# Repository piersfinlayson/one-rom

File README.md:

# One ROM

**[One ROM](https://onerom.org) - One ROM To Rule Them All**

The most flexible and powerful ROM replacement for your retro computer.  A single Raspberry Pi
RP2350-base board in the footprint of the original chip emulates 24, 28, 32 and
40 pin mask ROMs, EPROMs, EEPROMs, bipolar PROMs and some SRAM — and then does
things the original never could.  It serves several ROM sockets at once, switches
images at runtime, reprograms over USB without leaving the socket, talks back to
the machine it is installed in, and runs your own code as plugins.

Thousands of One ROMs are installed in Commodore 64s, VIC-20s, PETs, Amigas, BBCs, Ataris, TIs, Apple IIs,
disk drives, IBM PCs, pinball machines, drum machines, synthesizers and more.  It is
open source hardware and software, it is cheap to make, and it is actively
maintained and developed.

## New to One ROM?

**Start at [onerom.org](https://onerom.org).**  That is where the project is
explained and supported:

- [What One ROM is and why](https://onerom.org) — the overview, with pictures
- [Getting started](https://onerom.org/start/) — install it, program it, use it
- [Buy one](https://onerom.org/buy) — known vendors, if you'd rather not fab
  your own
- [Program from your browser](https://onerom.org/web) — no software to install

**The rest of this README is for people who want to build One ROM, hack on it,
or build things on top of it.**  If you just want a working ROM replacement, [onerom.org](https://onerom.org) will get you there faster.

## Ways in

One ROM is designed to be extended in many different ways.

| I want to… | Start here | Steps |
|------------|------------|------------|
| Drive a device from scripts or my own tooling | [Programming a One ROM](#programming-a-one-rom), [CLI manual](docs/CLI-MANUAL.md) | Install and run the CLI |
| Fab and assemble existing boards | [hardware/pcb](hardware/pcb/README.md) | Upload gerbers and BOM/POS files to a fab |
| Commission boards I've made | [Commissioning](docs/COMMISSIONING.md) | Request an authorised signing key or submit a signing request for a board |
| Build the firmware myself | [Building from source](#building-from-source) | Use `make` or the build container |
| Use the header pins as GPIOs — reset the host, drive a line | [Driving the host](#driving-the-host--gpio-and-reset) | One command, plus a wire for host reset |
| Add support for a chip type One ROM doesn't know | [Adding a chip type](docs/ADDING-CHIP-TYPES.md) | A JSON entry plus one line of Rust or a firmware and tooling update if no existing serving algorithm fits |
| Add support for a new board revision | [rust/config/json](rust/config/json/README.md) | A new JSON file once the board is designed |
| Write a plugin — from scratch, or from a working one | [Plugins](#plugins), [firmware/ora/examples](firmware/ora/examples) | C, against a stable API |
| Talk to the retro machine from the ROM socket | [RBCP](#rbcp--talking-to-the-host-system) | 6502 and 68000 host code provided |
| Build host-side tools of my own | [Rust crates](#rust-crates) | Rust, on published crates |
| Read and test real ROM chips | [One ROM Lab](#one-rom-lab) | Flash Lab to a spare Fire board |
| Add a serving algorithm, or change how serving works | [How the firmware works](#how-the-firmware-works) | Bare metal C, PIO and DMA, plus Rust tooling |
| Design a new board | [hardware/pcb](hardware/pcb/README.md) | KiCad |

## Hardware

One ROM comes in two families:

- **Fire** — RP2350, in 24, 28, 32 and 40 pin variants, latest boards include an
  RGB NeoPixel.  All development happens for these boards.
- **Ice** — STM32F4, 24 pin only.  Legacy: still supported with 0.6.x firmware,
  but it is not being enhanced.  The 0.7.x firmware and the CLI do not
  support it.

<div align="center">
    
</div>

<div align="center">
    
</div>

All the design files needed to manufacture your own are in
[hardware/pcb](hardware/pcb).  Start with the
[recommended revisions](hardware/pcb/README.md#recommended-revisions) and
read the fabrication notes in the same file before you order.  Boards can be
fabbed and assembled at JLCPCB and other manufacturers cheaply.

<div align="center">
    
</div>

<p align="center"><em>Three One ROM Fire 24s in a Commodore 64, serving BASIC,
KERNAL and the character ROM.</em></p>

## Programming a One ROM

There are three tools, all doing the same job over USB:

- **[One ROM Web](https://onerom.org/web)** — browser based, nothing to install,
  the best choice for most people.
- **[One ROM CLI](https://onerom.org/cli)** — the full device tool, and what the
  examples below use ([rust/cli](rust/cli)).
- **[One ROM Studio](https://onerom.org/studio)** — native desktop GUI for
  Windows, macOS and Linux ([rust/studio](rust/studio)).

The CLI is the complete interface: everything the device can do is reachable from
it.  Full reference in the [CLI manual](docs/CLI-MANUAL.md).

Find what is connected:

```bash
onerom scan
```

Build an image from a config file and flash it:

```bash
onerom program --config onerom-config/vic20-pal.json
```

Program chips straight from the command line, without a config file, adding the
USB plugin so the device stays on the bus while it serves:

```bash
onerom program --slot file=kernal.901227-03.bin,type=2364,cs1=active-low --plugin usb
```

Build a firmware binary without touching a device, and look inside one:

```bash
onerom firmware build --config onerom-config/vic20-pal.json --board fire-24-e --output /tmp/onerom.bin
onerom firmware inspect --firmware /tmp/onerom.bin
```

Read and write the ROM image live, while the host is running from it:

```bash
onerom peek live --address 0x100 --length 64
onerom poke live --address 0x100 --byte 0xEA
```

## Driving the host — GPIO and reset

The image select and X pins are not just jumpers.  They are GPIOs, and
One ROM will drive them for you — which means the ROM socket becomes a way to
manipulate the machine it is plugged into.

Run a wire from a pin to the host's reset line and you can reset the machine
after flashing a new image:

```bash
onerom control reset --pin sel_c
```

`sel_c` is a common choice — more boards have it than have X pins, and it is 5V
tolerant where it exists.  Any pin works with `--pin`.

<div align="center">
    
</div>

<p align="center"><em>A One ROM Fire 40 in an Amiga A500, with <code>Sel_C</code>
wired to the 68000's reset line.</em></p>

You can see what every pin is and what it is currently doing:

```bash
onerom inspect gpio --all
onerom inspect socket --chip-type 2364 --gpio
```

The same GPIOs are available to plugins, so a plugin can drive them
autonomously — hold the host in reset until something is ready, blink an
external LED on ROM activity, or drive whatever you have wired up.

## Plugins

Serving runs entirely on PIO and DMA, so both CPU cores are free.  Plugins are
separate binaries, written in C against a stable API in
[firmware/ora](firmware/ora), that run on those cores *while serving continues*.
Two run at once.  This is how One ROM gains functionality without needing to
fork the core firmware.

There are two types, **system** and **user**.  The difference is resources, not
authorship — each is built for a different flash slot with a different RAM and
stack allocation, and you can write either.  System is intended for official One
ROM plugins such as the USB stack, but nothing stops you replacing it with your
own.

| Plugin | Type | What it does |
|--------|------|--------------|
| [usb](plugins/system/usb) | system | The device's own USB stack, so a running One ROM stays on the bus.  Exposes the ROM being served for live read and write, and the `picobootx` extended PICOBOOT interface. |
| [host-control](plugins/user/host-control) | user | A full [RBCP](#rbcp--talking-to-the-host-system) implementation. |
| [rgb](plugins/user/rgb) | user | Cycles the NeoPixel on RGB boards.  Superseded by the USB plugin's RGB support, reached with `onerom control rgb`. |
| [activity](plugins/user/activity) | user | Blinks the status LED when the host is reading the ROM. |
| [blink](plugins/user/blink) | user | Minimal example. |

The firmware passes each plugin a lookup function at startup.  The plugin calls
it with the ID of the facility it wants, and gets back a function pointer.
Available that way: status LED and GPIO control, device and firmware metadata,
logging, memory allocation, the ROM and RAM slots being served, and the address
monitor that reports what the host is reading — which is what RBCP is built on.
New IDs are only ever added, never changed, and each plugin declares the minimum
firmware version it needs, which the firmware enforces before launching it.

Start with [plugins/README.md](plugins/README.md) for how plugins are built and
configured, [firmware/ora/api.h](firmware/ora/api.h) for the API, and
[firmware/ora/examples](firmware/ora/examples) for worked examples — including
one that patches the C64 kernal live and one that drives an LED from character
ROM accesses.

## RBCP — talking to the host system

The [ROM Bus Control Protocol](https://github.com/piersfinlayson/rom-bus-control-protocol)
is bidirectional communication between a retro machine and the ROM emulator
installed in it, carried over nothing but the ROM's own address and data buses.
No extra wiring.  The machine reads and writes ROM addresses, and One ROM
interprets them.

That opens up things a ROM socket has no business being able to do:

- remote debugging of code running on real hardware
- ROM-based bootloaders — `grub` for the C64
- dynamic patching of games and demos as they run

The device side is the [host-control](plugins/user/host-control) plugin.  The
specification lives in the RBCP repository, along with reference host
implementations for 6502 and 68000 — generic routines plus sample C64 kernal and
Amiga Kickstart bootloaders.

## One ROM Lab

[One ROM Lab](rust/lab/README.md) is alternate firmware for a spare Fire board that turns
its ROM socket into a bus reader and tester.  Flash it, connect over USB, and you
get an interactive shell.

Read a real chip in the socket, as a checksum, a hexdump or Intel HEX.  Verify
that a One ROM under test serves the right bytes and tristates its data lines
when deselected.  Auto-detect chip select polarity on an unmarked mask ROM by
brute-forcing the combinations.  Dump the board's pin map, socket pin to signal
to GPIO.  It is what Fire 40 boards are tested with before they ship.

```bash
cd rust/lab && scripts/flash.sh
```
## Building from source

Dependencies are listed in [INSTALL.md](INSTALL.md), or use the
[build container](ci/docker/README.md).  The ARM and
Emscripten toolchain versions are pinned (`ci/arm-toolchain-version`,
`ci/emscripten-version`), as are the documentation tools that render the PDF
editions (`ci/pandoc-version`, `ci/weasyprint-version`), so a firmware binary is byte-identical wherever it is
built.

Build the base firmware:

```bash
make
```

That produces `firmware/build/onerom-rp235x.bin` — one binary, for every Fire
board.  The ROM images, chip configuration and plugins are composed onto it by
the host-side tools.  To flash *your* build rather than a downloaded release,
pass it explicitly:

```bash
onerom program --config onerom-config/vic20-pal.json --base-firmware firmware/build/onerom-rp235x.bin
```

## How the firmware works

Worth knowing before you go digging in [firmware/](firmware):

**It is fully bare metal.**  No SDK, no HAL — not pico-sdk, not a vendor library.
C with its own startup code and its own linker scripts to keep it lean.

**Serving runs on PIO and DMA.**  The RP2350's PIO state machines watch the
address and chip select lines and DMA the right byte onto the data pins.  The CPU
is not in the critical path, which is what leaves both cores free for plugins.

**The chip type is not compiled in.**  The firmware knows nothing about a 2364 or
a 27C400.  It has a small set of parameterised serving algorithms, and the
host-side generator works out which algorithm and what arguments a given chip on
a given board needs, then writes that into the firmware metadata.

**It is one binary for all boards.**  Board differences are metadata too.

**Bad configuration is visible, not silent.**  An image the firmware cannot make
sense of drops it into limp mode, with an special LED blink pattern.

**The PIO programs are assembled on the device, at boot.**  Which program is
needed depends on the chip, the board's pin mapping and the configuration in
flash, none of which are known at build time.
[apio](https://github.com/piersfinlayson/apio) assembles them in C at runtime,
and disassembles them so a generated program can be read back and checked.

## Regression tested off-hardware

Every push runs the **real firmware C** — the source that ships on devices, not a
model of it — compiled for the host and linked against
[epio](https://github.com/piersfinlayson/epio), a cycle-exact RP2350 PIO
emulator, then driven over emulated bus cycles.

The sweep is hundreds of test runs covering all Fire board revisions, all supported
chip types, every configuration shape the firmware offers — single, banked,
multi-chip, 16-bit — and every chip select polarity combination.  Every address
of every image is compared against an independent copy, which is 10s of
millions of byte-level comparisons, plus checks that the data bus tristates for every
non-selected control line combination.

The plugin API is covered down to all API IDs, and the host-control plugin's own C source is run against a full suite of
conformance tests whose basis is the protocol specification rather than the
implementation.

CS-to-data latency is asserted to the exact cycle in **both**
directions, so serving getting a cycle slower — or a cycle faster, which would
mean the check had stopped discriminating — fails the build.

What it does not do today is anything analogue — voltage levels, bus loading,
propagation delay at a real pin — or USB.  Those need a board, which is what
[One ROM Lab](#one-rom-lab) is for.

## Rust crates

The host-side tooling is a Cargo workspace in [rust/](rust).  The crates marked
published are on crates.io, for host-side Rust development.

| Crate | Published | What it is for |
|-------|:---------:|----------------|
| [`onerom-gen`](rust/gen) | ✓ | Generates ROM images and firmware metadata.  The heart of the toolchain — turns a config plus some ROM files into something flashable. |
| [`onerom-config`](rust/config) | ✓ | The config model: chip types, board definitions, pin maps, JSON schema. |
| [`onerom-fw`](rust/fw) | ✓ | Fetches One ROM base firmware and ROM images. |
| [`onerom-fw-parser`](rust/fw-parser) | ✓ | Reads metadata back out of a firmware binary — what chips, what board, what version. |
| [`onerom-metadata`](rust/metadata) | ✓ | The embedded metadata schema itself. |
| [`onerom-lab-metadata`](rust/lab-metadata) | ✓ | One ROM Lab's metadata structures. |
| [`onerom-lab-parser`](rust/lab-parser) | ✓ | Reads One ROM Lab's metadata structures from a device or an image. |
| [`onerom-metadata-gen`](rust/metadata-gen) | ✓ | Turns a metadata schema into C headers and Rust source. |
| [`onerom-cli`](rust/cli) | ✓ | Everything the CLI does, minus the command line parsing.  Build on it rather than reimplementing USB device logic. The CLI binary is released at [onerom.org/cli](https://onerom.org/cli). |
| [`onerom-app`](rust/app) | ✓ | Transport-free logic shared by the CLI, Studio and the web tools. |
| [`onerom-studio`](rust/studio) | | The desktop GUI, released at [onerom.org/studio](https://onerom.org/studio). |
| [`onerom-lab`](rust/lab) | | One ROM Lab, above. |
| [`onerom-lab-bus`](rust/lab-bus) | | One ROM Lab's host bus timing. |
| [`onerom-signing-server`](rust/signing-server) | | Signs commissioning instances. |
| [`onerom-lens`](rust/lens) | | One ROM Lens — compiles the firmware emulator to WebAssembly and draws PIO and DMA activity as waveforms in a browser, cycle by cycle. |
| [`onerom-fw-emulator`](rust/fw-emulator) | | Compiles and runs the real firmware C on a host, PIOs and all. |
| [`onerom-fw-tester`](rust/fw-tester) | | Drives the emulator with generated configurations and checks the results. |
| [`onerom-plugin-tester`](rust/plugin-tester) | | The harness a plugin tester is built from — runs a plugin's own C against the emulated firmware. |
| [`onerom-rbcp-host`](rust/rbcp-host) | | An RBCP host. One ROM Lab uses it to query a One ROM over the ROM bus. |
| [`onerom-rbcp-tester`](rust/rbcp-tester) | | Drives the host-control plugin over emulated ROM bus cycles, as an RBCP host would. |
| [`onerom-usb-tester`](rust/usb-tester) | | Drives the USB system plugin's commands, log forwarding and GPIO control. |
| [`onerom-fw-driver`](rust/fw-driver), [`onerom-fw-geometry`](rust/fw-geometry) | | Pin geometry and GPIO bitmask helpers, shared and dependency-free by design. |
| [`fw-config-gen`](rust/fw-config-gen), [`schema-gen`](rust/schema-gen) | | Code and schema generators. |
| [`doc-gen`](rust/doc-gen) | | Checks the values in `docs/` and `onerom-config/README.md`. |

For in-browser use, [one-rom-wasm](https://github.com/piersfinlayson/one-rom-wasm)
wraps `onerom-gen` as WASM, and is what the
[browser programmer](https://onerom.org/web) in
[one-rom-site](https://github.com/piersfinlayson/one-rom-site) is built on.

## What is in this repository

| Directory | Contents |
|-----------|----------|
| [`firmware/`](firmware) | The core firmware: C and Thumb assembly, bare metal.  `ora/` is the plugin API. |
| [`plugins/`](plugins) | System and user plugins. |
| [`rust/`](rust) | The Cargo workspace — CLI, Studio, generators, emulator, Lab, Lens. |
| [`hardware/pcb/`](hardware/pcb) | KiCad designs, per board revision, verified and unverified. |
| [`onerom-config/`](onerom-config) | Ready-made JSON configs for some common systems, and the config schema. |
| [`docs/`](docs) | Documentation, including the generated chip and compatibility references. |
| [`ci/`](ci) | Build, test and lint scripts, and the reproducible build container. |
| [`images/`](images) | Test ROM images. |
| [`demo/`](demo) | Demonstration programs for the retro side. |

## Documentation

| Topic | Description |
|-------|-------------|
| [CLI Manual](docs/CLI-MANUAL.md) | Complete reference for the `onerom` command line tool. |
| [Chip Types](docs/CHIP-TYPES.md) | Every chip type One ROM knows about, with pinouts and control lines. |
| [Compatibility](docs/COMPATIBILITY.md) | Which chips each hardware variant can emulate, and at what flash cost. |
| [Adding a Chip Type](docs/ADDING-CHIP-TYPES.md) | Teaching One ROM to emulate a chip it does not yet know. |
| [Commissioning](docs/COMMISSIONING.md) | Setting a One ROM's hardware settings. |
| [Image Selection](docs/IMAGE-SELECTION.md) | Telling One ROM which installed image to serve. |
| [Logging](docs/LOGGING.md) | Reading One ROM's log, over USB or with a debug probe. |
| [Image Sets](docs/MULTI-ROM-SETS.md) | Serving several ROMs at once, and dynamic bank switching. |
| [Plugins](plugins/README.md) | Building, configuring and writing plugins. |
| [Build Container](ci/docker/README.md) | Building the firmware reproducibly in Docker. |
| [ROMs Glorious ROMs](docs/ROMS-GLORIOUS-ROMS.md) | Everything you wanted to know about 23/27 series ROMs but were afraid to ask. |
| [Second Flash](docs/SECOND-FLASH.md) | How One ROM handles a second flash chip connected to the RP2350 |
| [Changelog](CHANGELOG.md) | What changed, and when. |

The CLI manual, chip type and compatibility references are also published as
PDFs, in A4 and US Letter, at [onerom.org/docs](https://onerom.org/docs/).

More in [docs/](docs) — flash layout, voltage levels, using a Pi Pico as
an SWD programmer — plus [INSTALL.md](INSTALL.md) for build dependencies and
[LICENSE.md](LICENSE.md).

## Videos

Why use One ROM:

The hardware family:

## Related repositories

| Repository | What it is |
|------------|------------|
| [rom-bus-control-protocol](https://github.com/piersfinlayson/rom-bus-control-protocol) | The RBCP specification, and 6502/68000 reference host implementations. |
| [one-rom-site](https://github.com/piersfinlayson/one-rom-site) | onerom.org, including the browser programmer. |
| [one-rom-images](https://github.com/piersfinlayson/one-rom-images) | images.onerom.org — firmware images, configs, plugin manifests. |
| [one-rom-wasm](https://github.com/piersfinlayson/one-rom-wasm) | WASM build of `onerom-gen`, for in-browser firmware generation. |
| [picoboot](https://github.com/piersfinlayson/picoboot) | Host-side Rust crate for the RP2350 PICOBOOT USB interface. |
| [picobootx](https://github.com/piersfinlayson/picobootx) | Device-side PICOBOOT extension, exposed by the USB plugin. |
| [apio](https://github.com/piersfinlayson/apio) | Runtime RP2350 PIO assembler and disassembler. |
| [epio](https://github.com/piersfinlayson/epio) | Cycle-exact RP2350 PIO emulator. |

## Problems

Raise an issue at the [project issues page](https://github.com/piersfinlayson/one-rom/issues)
or start a thread at [GitHub Discussions](https://github.com/piersfinlayson/one-rom/discussions).
Please include:

- your One ROM PCB type and revision (or a photo if you're unsure)
- the retro system you are using it with
- details of the problem.

## Contributing

Pull requests are welcome — firmware, tools, hardware and documentation.  If you
write a plugin you think others would want to use, consider contributing it
so it can be published.  The plugins publishing process is documented in
[plugins/CONTRIBUTIONS](plugins/CONTRIBUTIONS.md)

## License

See [LICENSE](LICENSE.md) for software and hardware licensing information, and
[ACKNOWLEDGEMENTS](ACKNOWLEDGEMENTS.md) for third party work One ROM builds on
or is compatible with.

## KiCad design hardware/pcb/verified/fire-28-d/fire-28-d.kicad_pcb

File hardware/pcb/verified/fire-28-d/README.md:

# Fire 28 Rev D

An upright USB-C variant of fire-28-c - the connector sticks up out of the board rather than lying flat, which helps where there is too little room at the edge of One ROM to plug in a cable.  It is not preferred over fire-28-c - the two connector orientations are complementary.

**Has components on both sides of the board.**

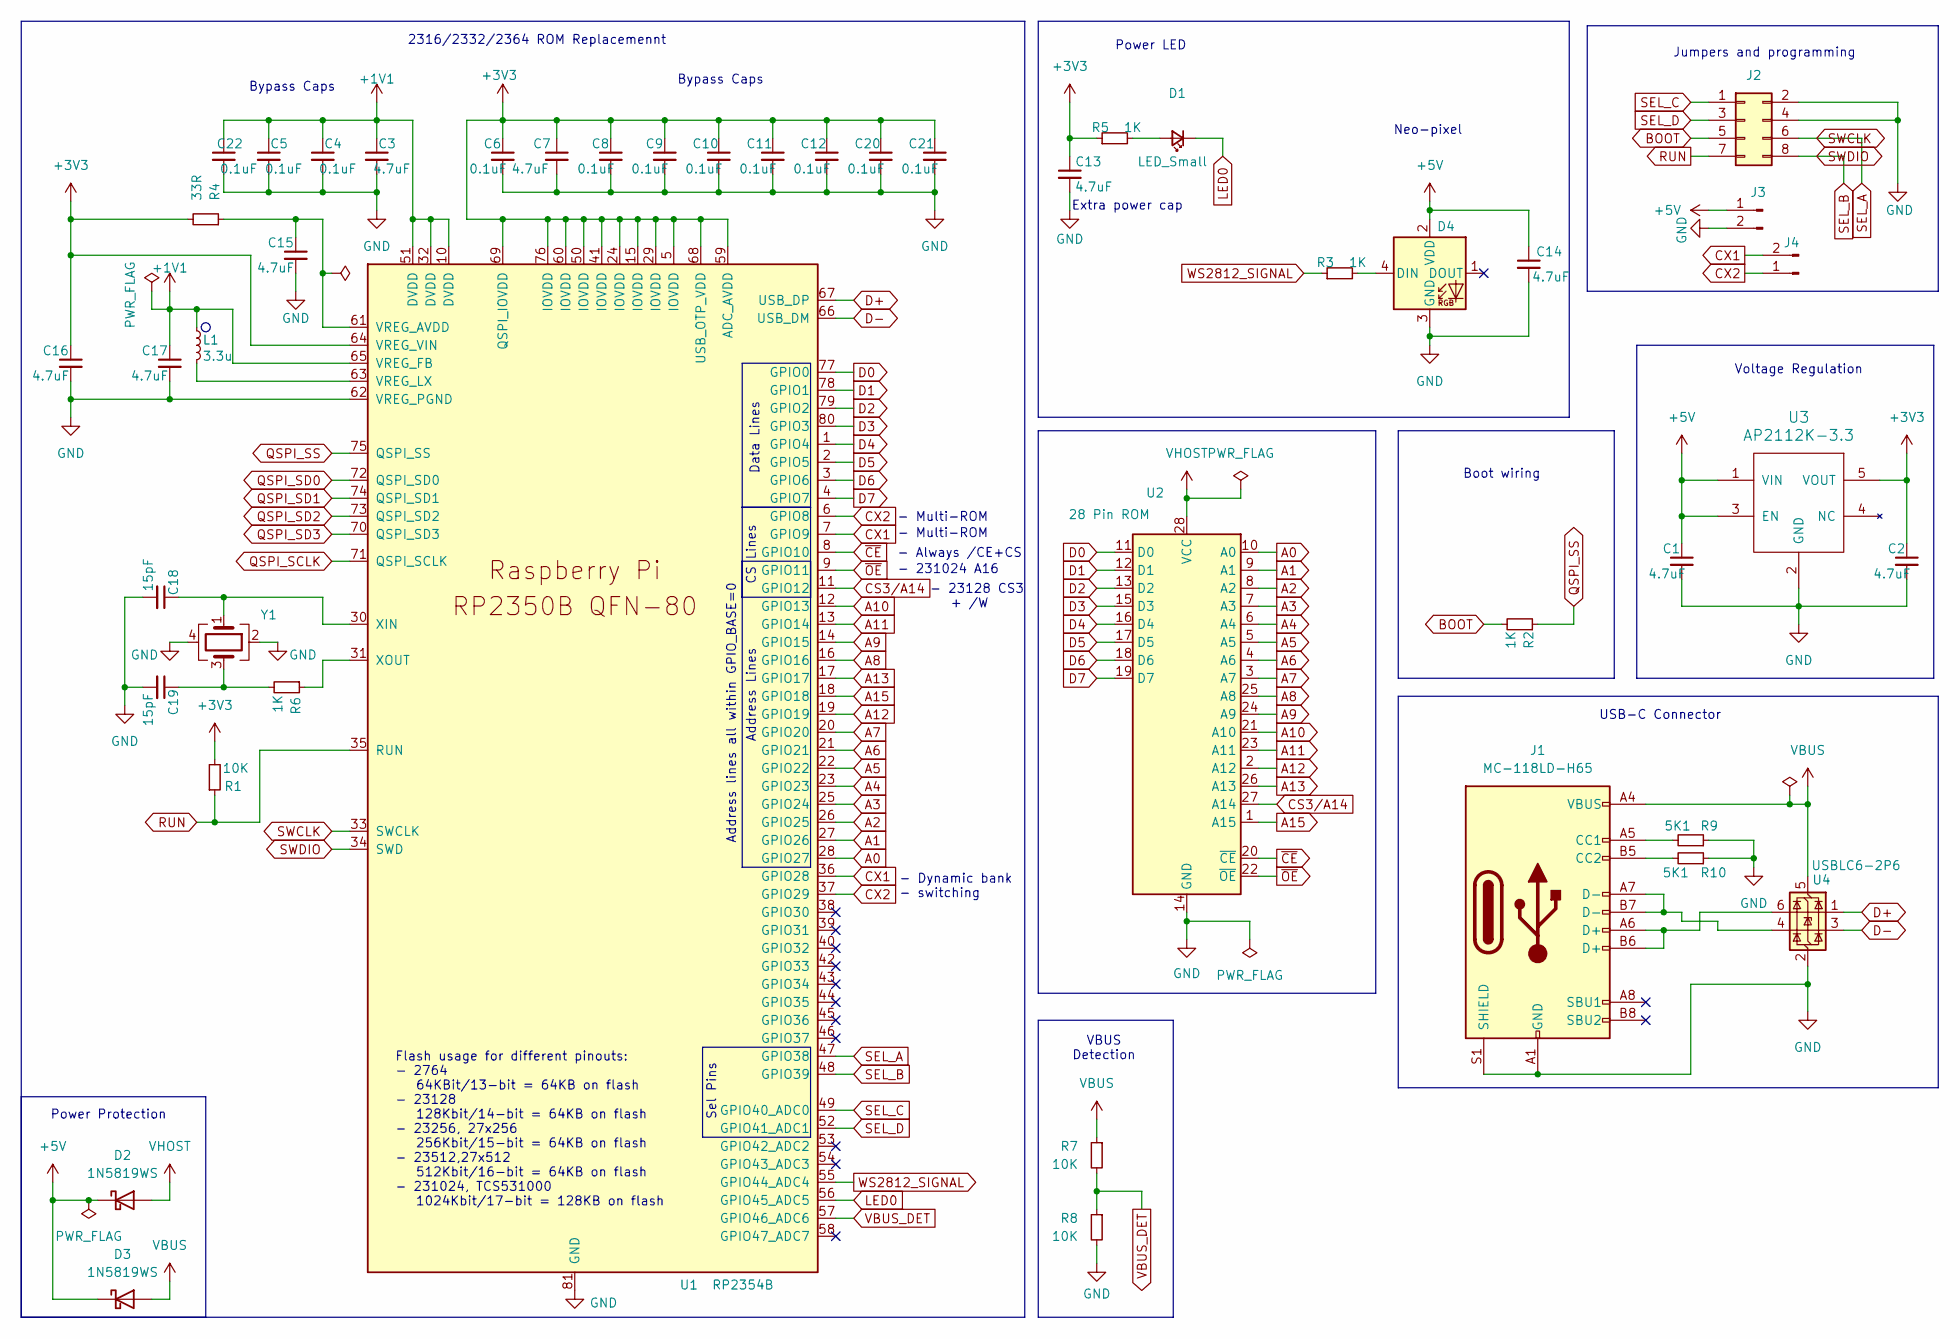
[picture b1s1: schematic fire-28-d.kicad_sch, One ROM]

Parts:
C1, C2, C3, C7, C13, C14, C15: 4.7uF; C_0402_1005Metric; LCSC C23733
C4, C5, C6, C8, C9, C10, C11, C12, C20, C21, C22: 0.1uF; C_0402_1005Metric; LCSC C1525
C16, C17: 4.7uF; C_0402_1005Metric_small_pads; LCSC C23733
C18, C19: 15pF; C_0402_1005Metric; LCSC C1548
D1: LED_Small; LED_0402_1005Metric; LCSC C25503345
D2, D3: 1N5819WS; D_SOD-323; LCSC C191023
D4: XL-1010RGBC-WS2812B; XL-1010RGBC-2812B; LCSC C5349953
J1: MC-118LD-H65; USB-C-upright-C6332304-hanbo-MC-118LD-H65; LCSC C6332304
J2: Conn_02x04_Odd_Even; PinHeader_2x04_P2.54mm_Vertical custom silkscreen
J3, J4: Conn_01x02_Pin; PinHeader_1x02_P2.54mm_Vertical
L1: 3.3u; L_pol_2016; LCSC C42411119
R1, R7, R8: 10K; R_0402_1005Metric; LCSC C25744
R2, R3, R5, R6: 1K; R_0402_1005Metric; LCSC C11702
R4: 33R; R_0402_1005Metric; LCSC C25105
R9, R10: 5K1; R_0402_1005Metric; LCSC C25905
U1: RP2354B; RP2350-QFN-80-1EP_10x10_P0.4mm_EP3.4x3.4mm_ThermalVias; LCSC C39843328
U2: 28 Pin ROM; 28 pin rom footprint
U3: AP2112K-3.3; SOT-23-5; LCSC C51118
U4: USBLC6-2P6; SOT-666; LCSC C15999
Y1: Crystal_GND24; Crystal_SMD_Abracon_ABM8G-4Pin_3.2x2.5mm; LCSC C20625731

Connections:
+1V1: C3.1, C4.1, C5.1, C17.1, C22.1, L1.1, U1.10 (DVDD), U1.32 (DVDD), U1.51 (DVDD), U1.65 (VREG_FB)
+3V3: C2.1, C6.1, C7.1, C8.1, C9.1, C10.1, C11.1, C12.1, C13.1, C16.1, C20.1, C21.1, R1.2, R4.2, R5.1, U1.5 (IOVDD), U1.15 (IOVDD), U1.24 (IOVDD), U1.29 (IOVDD), U1.41 (IOVDD), U1.50 (IOVDD), U1.59 (ADC_AVDD), U1.60 (IOVDD), U1.64 (VREG_VIN), U1.68 (USB_OTP_VDD), U1.69 (QSPI_IOVDD), U1.76 (IOVDD), U3.5 (VOUT)
+5V: C1.1, C14.1, D2.1 (K), D3.1 (K), D4.2 (VDD), J3.1, U3.1 (VIN), U3.3 (EN)
A0: U1.28 (GPIO27), U2.10 (A0)
A1: U1.27 (GPIO26), U2.9 (A1)
A2: U1.26 (GPIO25), U2.8 (A2)
A3: U1.25 (GPIO24), U2.7 (A3)
A4: U1.23 (GPIO23), U2.6 (A4)
A5: U1.22 (GPIO22), U2.5 (A5)
A6: U1.21 (GPIO21), U2.4 (A6)
A7: U1.20 (GPIO20), U2.3 (A7)
A8: U1.16 (GPIO16), U2.25 (A8)
A9: U1.14 (GPIO15), U2.24 (A9)
A10: U1.12 (GPIO13), U2.21 (A10)
A11: U1.13 (GPIO14), U2.23 (A11)
A12: U1.19 (GPIO19), U2.2 (A12)
A13: U1.17 (GPIO17), U2.26 (A13)
A15: U1.18 (GPIO18), U2.1 (A15)
BOOT: J2.5, R2.2
CS3/A14: U1.11 (GPIO12), U2.27 (A14)
CX1: J4.2, U1.7 (GPIO9), U1.36 (GPIO28)
CX2: J4.1, U1.6 (GPIO8), U1.37 (GPIO29)
D0: U1.77 (GPIO0), U2.11 (D0)
D1: U1.78 (GPIO1), U2.12 (D1)
D2: U1.79 (GPIO2), U2.13 (D2)
D3: U1.80 (GPIO3), U2.15 (D3)
D4: U1.1 (GPIO4), U2.16 (D4)
D5: U1.2 (GPIO5), U2.17 (D5)
D6: U1.3 (GPIO6), U2.18 (D6)
D7: U1.4 (GPIO7), U2.19 (D7)
D+: U1.67 (USB_DP), U4.1 (I/O1)
D-: U1.66 (USB_DM), U4.3 (I/O2)
GND: C1.2, C2.2, C3.2, C4.2, C5.2, C6.2, C7.2, C8.2, C9.2, C10.2, C11.2, C12.2, C13.2, C14.2, C15.2, C16.2, C17.2, C18.2, C19.2, C20.2, C21.2, C22.2, D4.3 (GND), J1.A1 (GND), J1.A12 (GND), J1.B1 (GND), J1.B12 (GND), J1.S1 (SHIELD), J2.2, J2.4, J3.2, R8.2, R9.1, R10.1, U1.62 (VREG_PGND), U1.81 (GND), U2.14 (GND), U3.2 (GND), U4.2 (GND), Y1.2, Y1.4
LED0: D1.1 (K), U1.56 (GPIO45_ADC5)
unnamed: C19.1, R6.2, Y1.3
unnamed: D1.2 (A), R5.2
unnamed: D4.4 (DIN), R3.2
unnamed: J1.A5 (CC1), R9.2
unnamed: J1.B5 (CC2), R10.2
unnamed: J1.A6 (D+), J1.B6 (D+), U4.6 (I/O1)
unnamed: J1.A7 (D-), J1.B7 (D-), U4.4 (I/O2)
unnamed: C15.1, R4.1, U1.61 (VREG_AVDD)
unnamed: L1.2, U1.63 (VREG_LX)
unnamed: C18.1, U1.30 (XIN), Y1.1
unnamed: R6.1, U1.31 (XOUT)
QSPI_SCLK: U1.71 (QSPI_SCLK)
QSPI_SD0: U1.72 (QSPI_SD0)
QSPI_SD1: U1.74 (QSPI_SD1)
QSPI_SD2: U1.73 (QSPI_SD2)
QSPI_SD3: U1.70 (QSPI_SD3)
QSPI_SS: R2.1, U1.75 (QSPI_SS)
RUN: J2.7, R1.1, U1.35 (RUN)
SEL_A: J2.6, U1.33 (SWCLK), U1.47 (GPIO38)
SEL_B: J2.8, U1.34 (SWD), U1.48 (GPIO39)
SEL_C: J2.1, U1.49 (GPIO40_ADC0)
SEL_D: J2.3, U1.52 (GPIO41_ADC1)
VBUS: D3.2 (A), J1.A4 (VBUS), J1.A9 (VBUS), J1.B4 (VBUS), J1.B9 (VBUS), R7.1, U4.5 (VBUS)
VBUS_DET: R7.2, R8.1, U1.57 (GPIO46_ADC6)
VHOST: D2.2 (A), U2.28 (VCC)
WS2812_SIGNAL: R3.1, U1.55 (GPIO44_ADC4)
~CE: U1.8 (GPIO10), U2.20 (~CE)
~OE: U1.9 (GPIO11), U2.22 (~OE)

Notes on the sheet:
- Multi-ROM
Data Lines
USB-C Connector
Address lines all within GPIO_BASE=0
Voltage Regulation
- Dynamic bank - switching
Extra power cap
Neo-pixel
CS Lines
2316/2332/2364 ROM Replacemennt
Bypass Caps
Power LED
- 23128 CS3 + /W
Power Protection
- 231024 A16
Address Lines
Boot wiring
Sel Pins
VBUS Detection
- Always /CE+CS
Flash usage for different pinouts: - 2764 64KBit/13-bit = 64KB on flash - 23128 128Kbit/14-bit = 64KB on flash - 23256, 27x256 256Kbit/15-bit = 64KB on flash - 23512,27x512 512Kbit/16-bit = 64KB on flash - 231024, TCS531000 1024Kbit/17-bit = 128KB on flash
Jumpers and programming

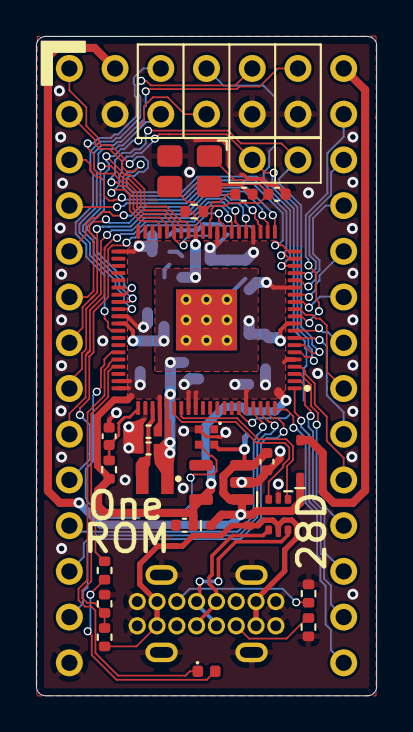
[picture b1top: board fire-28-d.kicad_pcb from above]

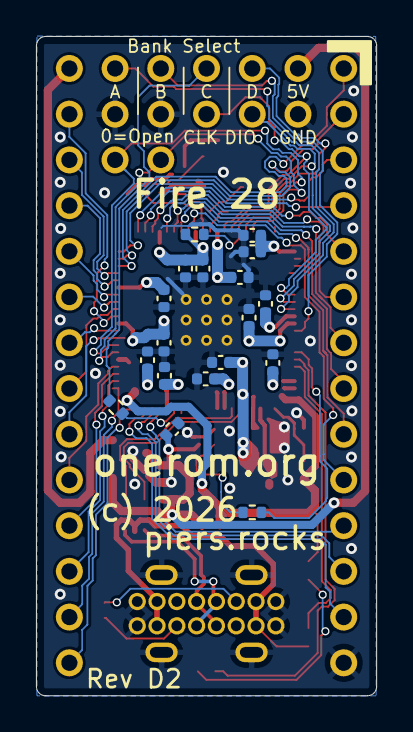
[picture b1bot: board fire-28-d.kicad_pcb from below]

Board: 2 copper layers, 18.9 x 36.6 mm, 46 parts (18 on the bottom side), 57 nets.

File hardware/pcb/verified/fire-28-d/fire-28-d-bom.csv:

"Reference","Qty","Value","DNP","Exclude from BOM","Exclude from Board","Footprint","Datasheet","LCSC"
"C1,C2,C3,C7,C13,C14,C15,C16,C17","9","4.7uF","","","","Capacitor_SMD:C_0402_1005Metric","~","C23733"
"C4,C5,C6,C8,C9,C10,C11,C12,C20,C21,C22","11","0.1uF","","","","Capacitor_SMD:C_0402_1005Metric","~","C1525"
"C18,C19","2","15pF","","","","Capacitor_SMD:C_0402_1005Metric","~","C1548"
"D1","1","LED_Small","","","","LED_SMD:LED_0402_1005Metric","~","C25503345"
"D2,D3","2","1N5819WS","","","","Diode_SMD:D_SOD-323","","C191023"
"D4","1","XL-1010RGBC-WS2812B","","","","piers retro:XL-1010RGBC-2812B","https://jlcpcb.com/partdetail/XINGLIGHT-XL_1010RGBC2812B/C5349953","C5349953"
"J1","1","MC-118LD-H65","","","","piers retro:USB-C-upright-C6332304-hanbo-MC-118LD-H65","https://jlcpcb.com/api/file/downloadByFileSystemAccessId/859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","C6332304"
"L1","1","3.3u","","","","RP2350_60QFN_minimal:L_pol_2016","~","C42411119"
"R1,R7,R8","3","10K","","","","Resistor_SMD:R_0402_1005Metric","~","C25744"
"R2,R3,R5,R6","4","1K","","","","Resistor_SMD:R_0402_1005Metric","~","C11702"
"R4","1","33R","","","","Resistor_SMD:R_0402_1005Metric","~","C25105"
"R9,R10","2","5K1","","","","Resistor_SMD:R_0402_1005Metric","~","C25905"
"U1","1","RP2354B","","","","RP2350B:RP2350-QFN-80-1EP_10x10_P0.4mm_EP3.4x3.4mm_ThermalVias",""," C39843328"
"U3","1","AP2112K-3.3","","","","Package_TO_SOT_SMD:SOT-23-5","","C51118"
"U4","1","USBLC6-2P6","","","","Package_TO_SOT_SMD:SOT-666","https://www.st.com/resource/en/datasheet/usblc6-2.pdf","C15999"
"Y1","1","Crystal_GND24","","","","Crystal:Crystal_SMD_Abracon_ABM8G-4Pin_3.2x2.5mm","~","C20625731"

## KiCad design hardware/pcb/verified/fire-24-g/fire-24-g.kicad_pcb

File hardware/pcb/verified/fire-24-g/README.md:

# Fire 24 Rev G

An upright USB-C variant of fire-24-f - the connector sticks up out of the board rather than lying flat, which helps where there is too little room at the edge of One ROM to plug in a cable.  It is not preferred over fire-24-f - the two connector orientations are complementary.

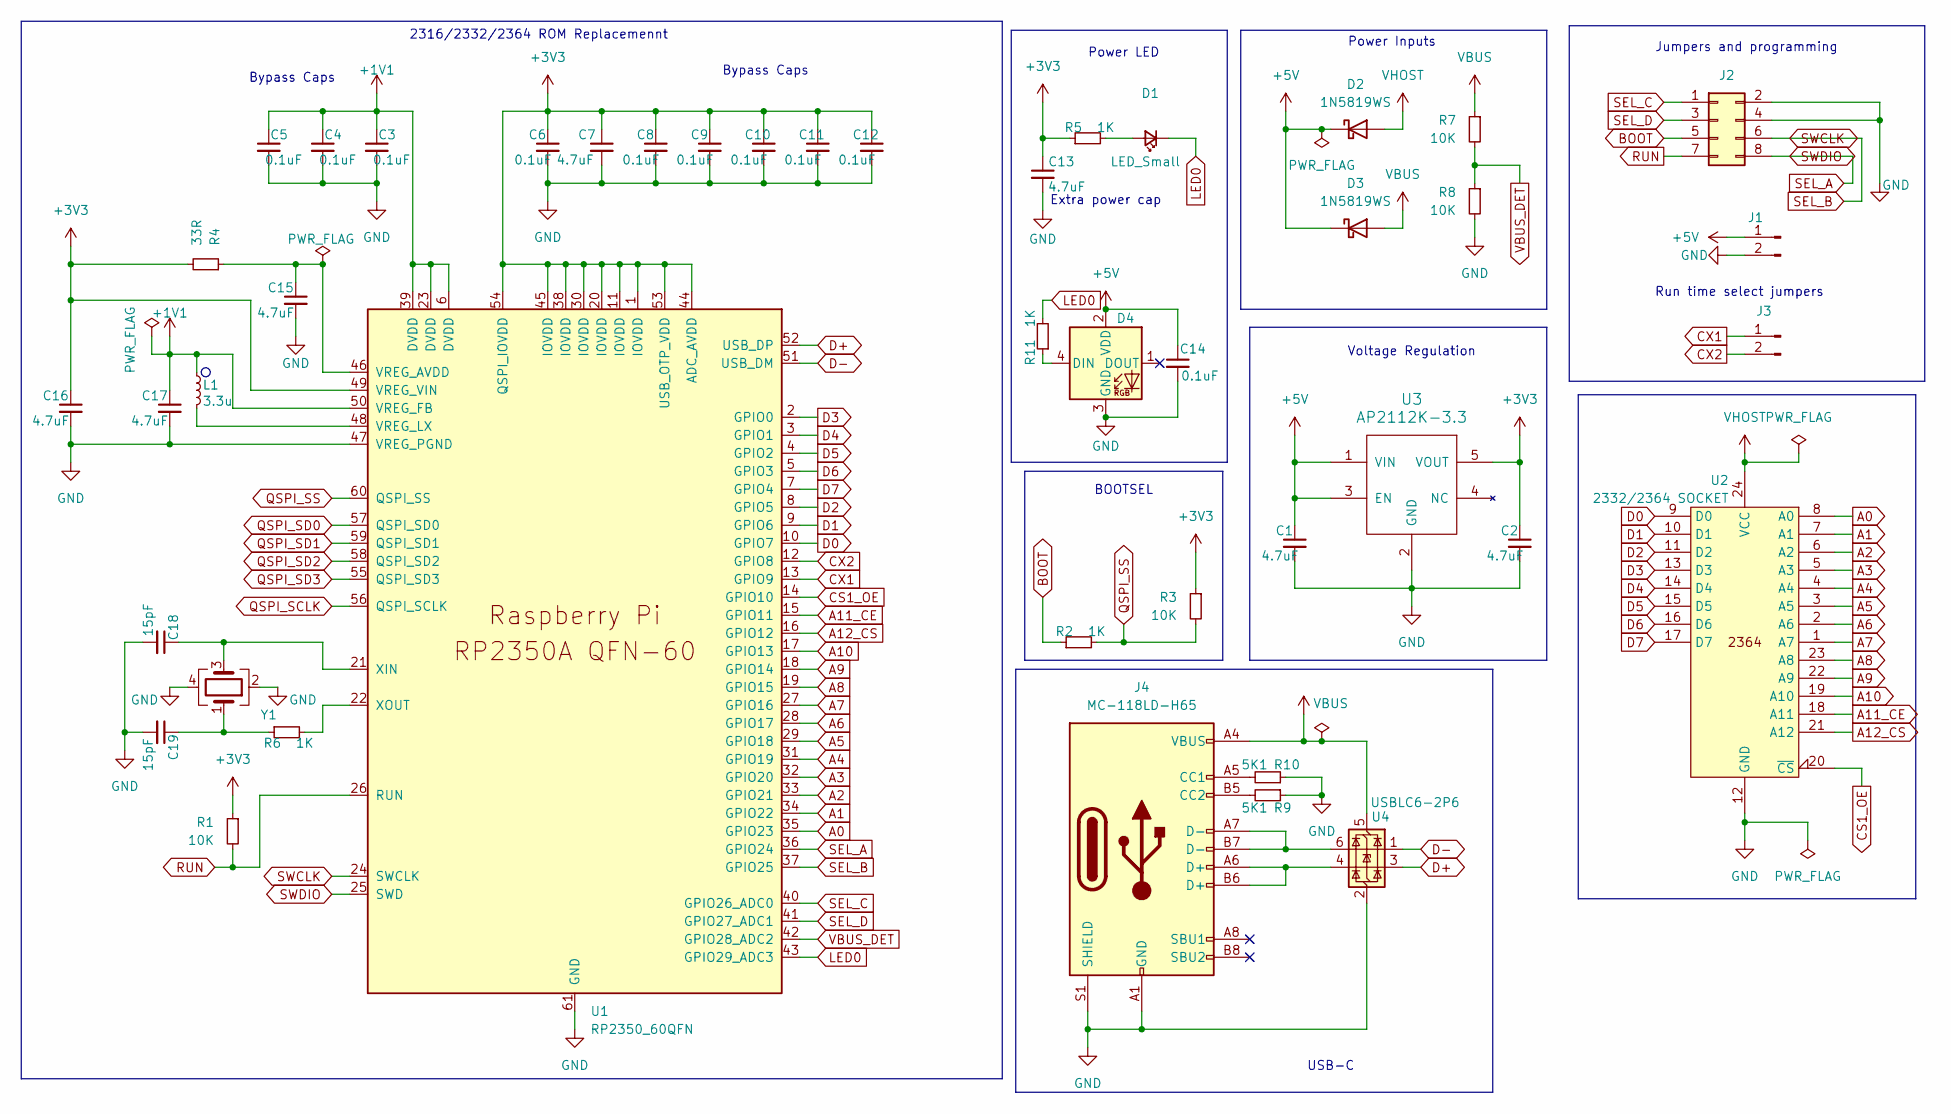
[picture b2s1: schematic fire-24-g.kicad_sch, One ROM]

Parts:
C1, C2, C7, C13, C15: 4.7uF; C_0402_1005Metric; LCSC C23733
C3, C4, C5, C6, C8, C9, C10, C11, C12, C14: 0.1uF; C_0201_0603Metric; LCSC C668346
C16, C17: 4.7uF; C_0402_1005Metric_small_pads; LCSC C23733
C18, C19: 15pF; C_0201_0603Metric; LCSC C85891
D1: LED_Small; LED_0402_1005Metric; LCSC C25503345
D2, D3: 1N5819WS; D_SOD-323; LCSC C191023
D4: XL-1010RGBC-WS2812B; XL-1010RGBC-2812B; LCSC C5349953
J1, J3: Conn_01x02_Pin; PinHeader_1x02_P2.54mm_Vertical
J2: Conn_02x04_Odd_Even; PinHeader_2x04_P2.54mm_Vertical custom silkscreen
J4: MC-118LD-H65; USB-C-upright-C6332304-hanbo-MC-118LD-H65; LCSC C6332304
L1: 3.3u; L_pol_2016; LCSC C42411119
R1, R3, R7, R8: 10K; R_0201_0603Metric; LCSC C473048
R2, R5, R6, R11: 1K; R_0201_0603Metric; LCSC C270365
R4: 33R; R_0402_1005Metric; LCSC C25105
R9, R10: 5K1; R_0201_0603Metric; LCSC C270344
U1: RP2350_60QFN; RP2350-QFN-60-1EP_7x7_P0.4mm_EP3.4x3.4mm_ThermalVias; LCSC C41378174
U2: 2332/2364 SOCKET; 2x12 dip pin output 600mil centres no ss
U3: AP2112K-3.3; SOT-23-5; LCSC C51118
U4: USBLC6-2P6; SOT-666; LCSC C15999
Y1: Crystal_GND24; Crystal_SMD_Abracon_ABM8G-4Pin_3.2x2.5mm; LCSC C20625731

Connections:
+1V1: C3.1, C4.1, C5.1, C17.1, L1.1, U1.6 (DVDD), U1.23 (DVDD), U1.39 (DVDD), U1.50 (VREG_FB)
+3V3: C2.1, C6.1, C7.1, C8.1, C9.1, C10.1, C11.1, C12.1, C13.1, C16.1, R1.1, R3.1, R4.2, R5.1, U1.1 (IOVDD), U1.11 (IOVDD), U1.20 (IOVDD), U1.30 (IOVDD), U1.38 (IOVDD), U1.44 (ADC_AVDD), U1.45 (IOVDD), U1.49 (VREG_VIN), U1.53 (USB_OTP_VDD), U1.54 (QSPI_IOVDD), U3.5 (VOUT)
+5V: C1.1, C14.1, D2.1 (K), D3.1 (K), D4.2 (VDD), J1.1, U3.1 (VIN), U3.3 (EN)
A0: U1.35 (GPIO23), U2.8 (A0)
A1: U1.34 (GPIO22), U2.7 (A1)
A2: U1.33 (GPIO21), U2.6 (A2)
A3: U1.32 (GPIO20), U2.5 (A3)
A4: U1.31 (GPIO19), U2.4 (A4)
A5: U1.29 (GPIO18), U2.3 (A5)
A6: U1.28 (GPIO17), U2.2 (A6)
A7: U1.27 (GPIO16), U2.1 (A7)
A8: U1.19 (GPIO15), U2.23 (A8)
A9: U1.18 (GPIO14), U2.22 (A9)
A10: U1.17 (GPIO13), U2.19 (A10)
A11_CE: U1.15 (GPIO11), U2.18 (A11)
A12_CS: U1.16 (GPIO12), U2.21 (A12)
BOOT: J2.5, R2.1
CS1_OE: U1.14 (GPIO10), U2.20 (~CS)
CX1: J3.1, U1.13 (GPIO9)
CX2: J3.2, U1.12 (GPIO8)
D0: U1.10 (GPIO7), U2.9 (D0)
D1: U1.9 (GPIO6), U2.10 (D1)
D2: U1.8 (GPIO5), U2.11 (D2)
D3: U1.2 (GPIO0), U2.13 (D3)
D4: U1.3 (GPIO1), U2.14 (D4)
D5: U1.4 (GPIO2), U2.15 (D5)
D6: U1.5 (GPIO3), U2.16 (D6)
D7: U1.7 (GPIO4), U2.17 (D7)
D+: U1.52 (USB_DP), U4.3 (I/O2)
D-: U1.51 (USB_DM), U4.1 (I/O1)
GND: C1.2, C2.2, C3.2, C4.2, C5.2, C6.2, C7.2, C8.2, C9.2, C10.2, C11.2, C12.2, C13.2, C14.2, C15.2, C16.2, C17.2, C18.2, C19.2, D4.3 (GND), J1.2, J2.2, J2.4, J4.A1 (GND), J4.A12 (GND), J4.B1 (GND), J4.B12 (GND), J4.S1 (SHIELD), R8.2, R9.1, R10.1, U1.47 (VREG_PGND), U1.61 (GND), U2.12 (GND), U3.2 (GND), U4.2 (GND), Y1.2, Y1.4
LED0: D1.1 (K), R11.2, U1.43 (GPIO29_ADC3)
unnamed: C19.1, R6.1, Y1.1
unnamed: D1.2 (A), R5.2
unnamed: D4.4 (DIN), R11.1
unnamed: J4.A5 (CC1), R10.2
unnamed: J4.B5 (CC2), R9.2
unnamed: J4.A6 (D+), J4.B6 (D+), U4.4 (I/O2)
unnamed: J4.A7 (D-), J4.B7 (D-), U4.6 (I/O1)
unnamed: C15.1, R4.1, U1.46 (VREG_AVDD)
unnamed: L1.2, U1.48 (VREG_LX)
unnamed: C18.1, U1.21 (XIN), Y1.3
unnamed: R6.2, U1.22 (XOUT)
QSPI_SCLK: U1.56 (QSPI_SCLK)
QSPI_SD0: U1.57 (QSPI_SD0)
QSPI_SD1: U1.59 (QSPI_SD1)
QSPI_SD2: U1.58 (QSPI_SD2)
QSPI_SD3: U1.55 (QSPI_SD3)
QSPI_SS: R2.2, R3.2, U1.60 (QSPI_SS)
RUN: J2.7, R1.2, U1.26 (RUN)
SEL_A: J2.8, U1.25 (SWD), U1.36 (GPIO24)
SEL_B: J2.6, U1.24 (SWCLK), U1.37 (GPIO25)
SEL_C: J2.1, U1.40 (GPIO26_ADC0)
SEL_D: J2.3, U1.41 (GPIO27_ADC1)
VBUS: D3.2 (A), J4.A4 (VBUS), J4.A9 (VBUS), J4.B4 (VBUS), J4.B9 (VBUS), R7.1, U4.5 (VBUS)
VBUS_DET: R7.2, R8.1, U1.42 (GPIO28_ADC2)
VHOST: D2.2 (A), U2.24 (VCC)

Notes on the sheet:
Run time select jumpers
Voltage Regulation
Power Inputs
USB-C
Extra power cap
2316/2332/2364 ROM Replacemennt
Bypass Caps
Power LED
BOOTSEL
Jumpers and programming

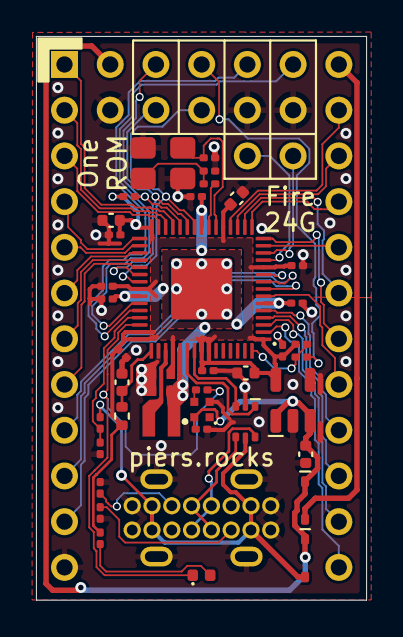
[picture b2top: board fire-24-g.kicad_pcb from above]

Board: 2 copper layers, 18.3 x 31.3 mm, 44 parts (0 on the bottom side), 52 nets.

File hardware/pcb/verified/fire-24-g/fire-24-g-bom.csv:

"Reference","Qty","Value","DNP","Exclude from BOM","Exclude from Board","Footprint","Datasheet","LCSC"
"C1,C2,C7,C13,C15,C16,C17","7","4.7uF","","","","Capacitor_SMD:C_0402_1005Metric","~","C23733"
"C3,C4,C5,C6,C8,C9,C10,C11,C12,C14","10","0.1uF","","","","Capacitor_SMD:C_0201_0603Metric","~","C307380"
"C18,C19","2","15pF","","","","Capacitor_SMD:C_0201_0603Metric","~","C85891"
"D1","1","LED_Small","","","","LED_SMD:LED_0402_1005Metric","~","C25503345"
"D2,D3","2","1N5819WS","","","","Diode_SMD:D_SOD-323","","C191023"
"D4","1","XL-1010RGBC-WS2812B","","","","piers retro:XL-1010RGBC-2812B","https://jlcpcb.com/partdetail/XINGLIGHT-XL_1010RGBC2812B/C5349953","C5349953 "
"J4","1","MC-118LD-H65","","","","piers retro:USB-C-upright-C6332304-hanbo-MC-118LD-H65","https://jlcpcb.com/api/file/downloadByFileSystemAccessId/859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","C6332304"
"L1","1","3.3u","","","","RP2350_60QFN_minimal:L_pol_2016","~","C42411119"
"R1,R3,R7,R8","4","10K","","","","Resistor_SMD:R_0201_0603Metric","~","C473048"
"R2,R5,R6,R11","4","1K","","","","Resistor_SMD:R_0201_0603Metric","~","C270365"
"R4","1","33R","","","","Resistor_SMD:R_0402_1005Metric","~","C25105"
"R9,R10","2","5K1","","","","Resistor_SMD:R_0201_0603Metric","~","C270344"
"U1","1","RP2350_60QFN","","","","RP2350_60QFN_minimal:RP2350-QFN-60-1EP_7x7_P0.4mm_EP3.4x3.4mm_ThermalVias",""," C41378174"
"U3","1","AP2112K-3.3","","","","Package_TO_SOT_SMD:SOT-23-5","","C51118"
"U4","1","USBLC6-2P6","","","","Package_TO_SOT_SMD:SOT-666","https://www.st.com/resource/en/datasheet/usblc6-2.pdf","C15999"
"Y1","1","Crystal_GND24","","","","Crystal:Crystal_SMD_Abracon_ABM8G-4Pin_3.2x2.5mm","~","C20625731"

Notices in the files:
rust/cli/src/board_view.rs:
Copyright (C) 2026 Piers Finlayson <piers@piers.rocks>
MIT License
hardware/pcb/verified/fire-24-g/fire-24-g.kicad_pcb:
(c) 2026 piers.rocks
hardware/pcb/verified/fire-28-b/kicad/fire-28-b.kicad_pcb:
(c) 2026
